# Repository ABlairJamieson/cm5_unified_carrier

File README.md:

# CM5 Unified Carrier

Carrier board for Radxa CM5 used in the Hyper-K camera system.

Features:
- 48V input
- PoE option
- USB3 camera interface
- Ethernet
- Uses drop in DC/DC modules for 48V->12V (ext power mode)
- Uses drop in DC/DC module for 12V->8V (IWCD camera)
- Uses drop in DC/DC module for 12V->5V (both cameras)

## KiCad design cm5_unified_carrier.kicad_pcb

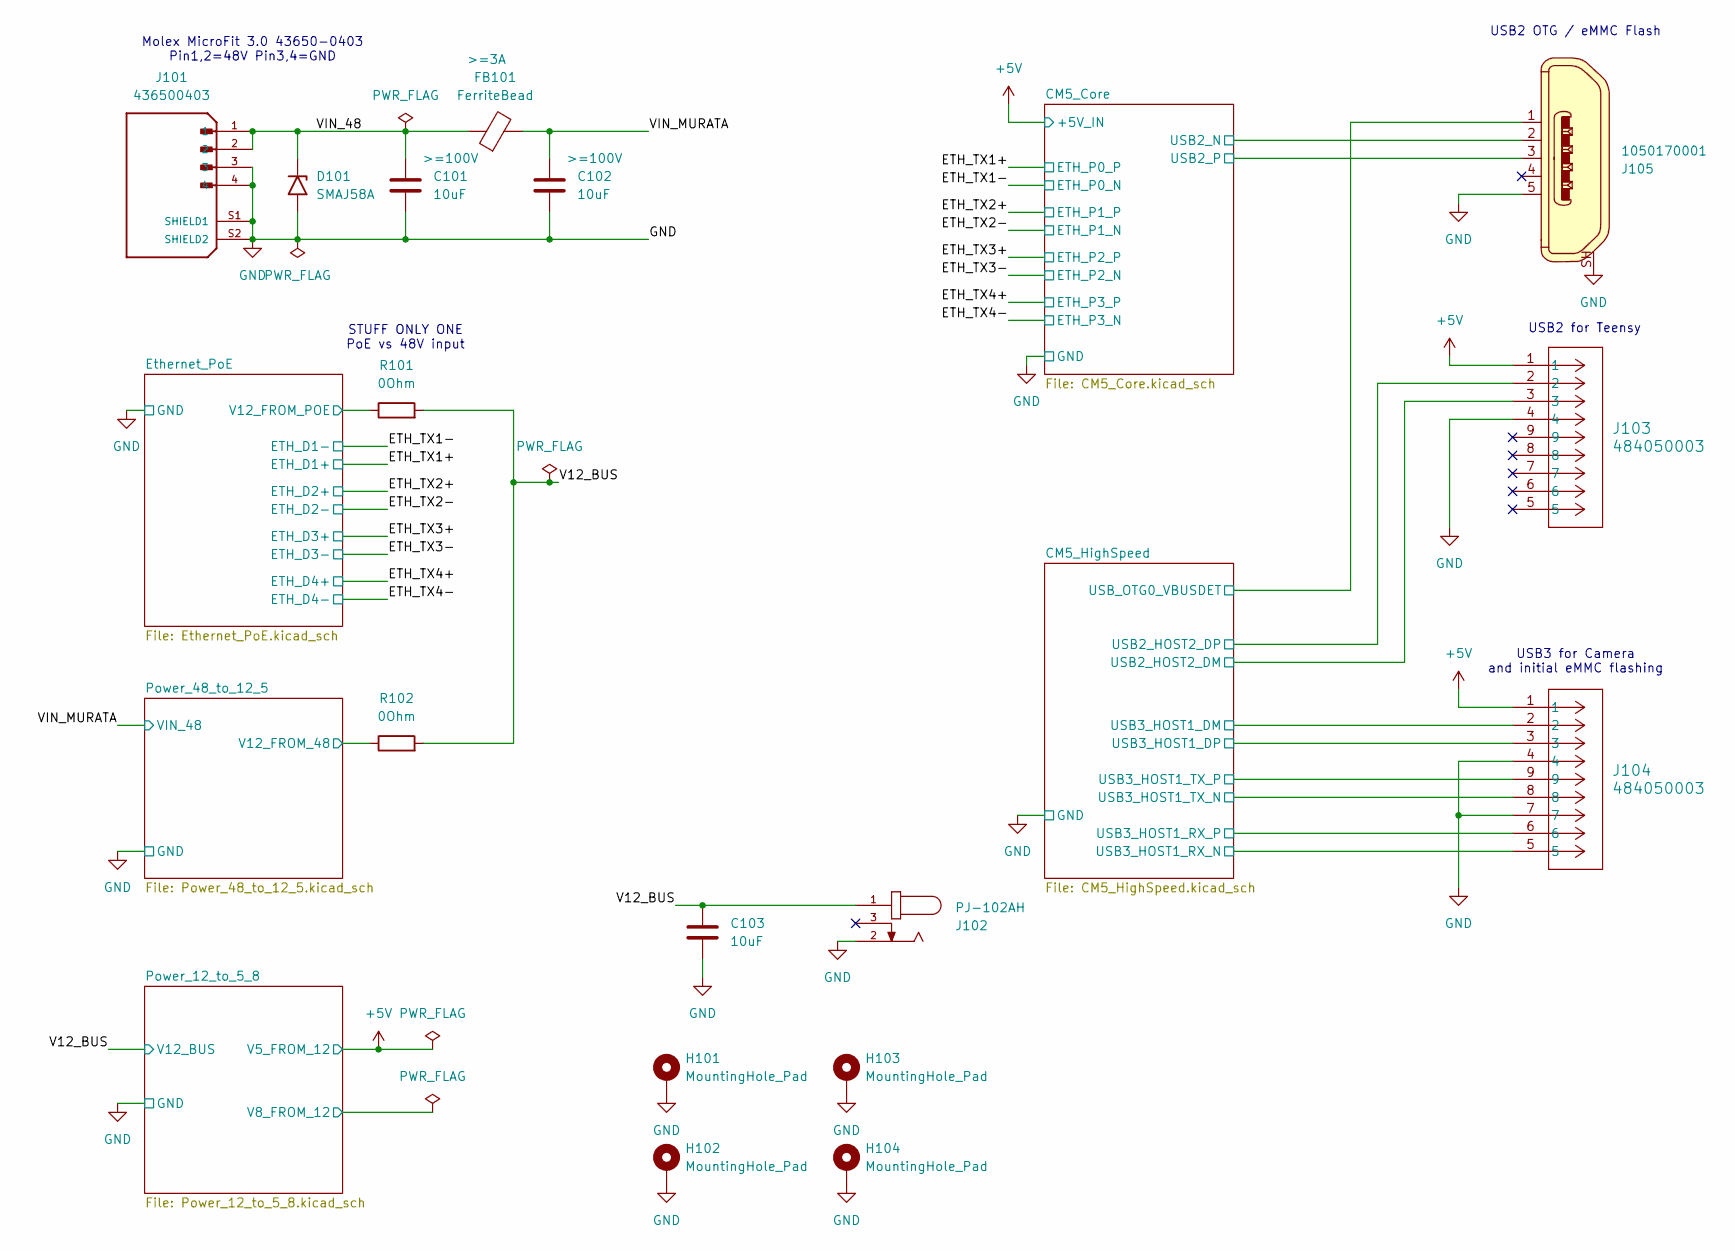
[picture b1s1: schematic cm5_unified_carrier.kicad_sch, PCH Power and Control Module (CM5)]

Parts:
C101, C102, C103: 10uF; C_1206_3216Metric_Pad1.33x1.80mm_HandSolder
D101: SMAJ58A; D_SMA
FB101: FerriteBead; FB_Wurth_WE-CBF-1206_W5.2
H101, H102, H103, H104: MountingHole_Pad; MountingHole_3.2mm_M3_DIN965_Pad
J101: 436500403; MOLEX_436500403; PARTREV F3
J102: PJ-102AH; CUI_PJ-102AH
J103, J104: 484050003; CONN_484050003_MOL
J105: 1050170001; USB_Micro_B_Female_1050170001; MPN 1050170001; Digi-Key_PN WM1399CT-ND
R101, R102: 0Ohm; R_1206_3216Metric_Pad1.30x1.75mm_HandSolder

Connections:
+5V: J103.1, J104.1; also elsewhere on the board
/CM5_Core/USB2_N: J105.2; also elsewhere on the board
/CM5_Core/USB2_P: J105.3; also elsewhere on the board
/CM5_HighSpeed/USB2_HOST2_DM: J103.3; also elsewhere on the board
/CM5_HighSpeed/USB2_HOST2_DP: J103.2; also elsewhere on the board
/CM5_HighSpeed/USB3_HOST1_DM: J104.2; also elsewhere on the board
/CM5_HighSpeed/USB3_HOST1_DP: J104.3; also elsewhere on the board
/CM5_HighSpeed/USB3_HOST1_SSRXN: J104.5; also elsewhere on the board
/CM5_HighSpeed/USB3_HOST1_SSRXP: J104.6; also elsewhere on the board
/CM5_HighSpeed/USB3_HOST1_SSTXN: J104.8; also elsewhere on the board
/CM5_HighSpeed/USB3_HOST1_SSTXP: J104.9; also elsewhere on the board
/CM5_HighSpeed/USB_OTG0_VBUSDET: J105.1; also elsewhere on the board
/Ethernet_PoE/V12_FROM_POE: R101.1; also elsewhere on the board
/Power_48_to_12_5/V12_FROM_48: R102.1; also elsewhere on the board
/V12_BUS: C103.1, J102.1, R101.2, R102.2; also elsewhere on the board
/VIN_48: C101.1, D101.1 (A1), FB101.1, J101.1, J101.2
/VIN_MURATA: C102.1, FB101.2; also elsewhere on the board
GND: C101.2, C102.2, C103.2, D101.2 (A2), H101.1, H102.1, H103.1, H104.1, J101.3, J101.4, J101.S1 (SHIELD1), J101.S2 (SHIELD2), J102.2, J103.4, J104.4, J104.7, J105.5, J105.SH; also elsewhere on the board

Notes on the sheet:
STUFF ONLY ONE PoE vs 48V input
USB2 for Teensy
USB2 OTG / eMMC Flash
USB3 for Camera and initial eMMC flashing
Molex MicroFit 3.0 43650-0403 Pin1,2=48V Pin3,4=GND

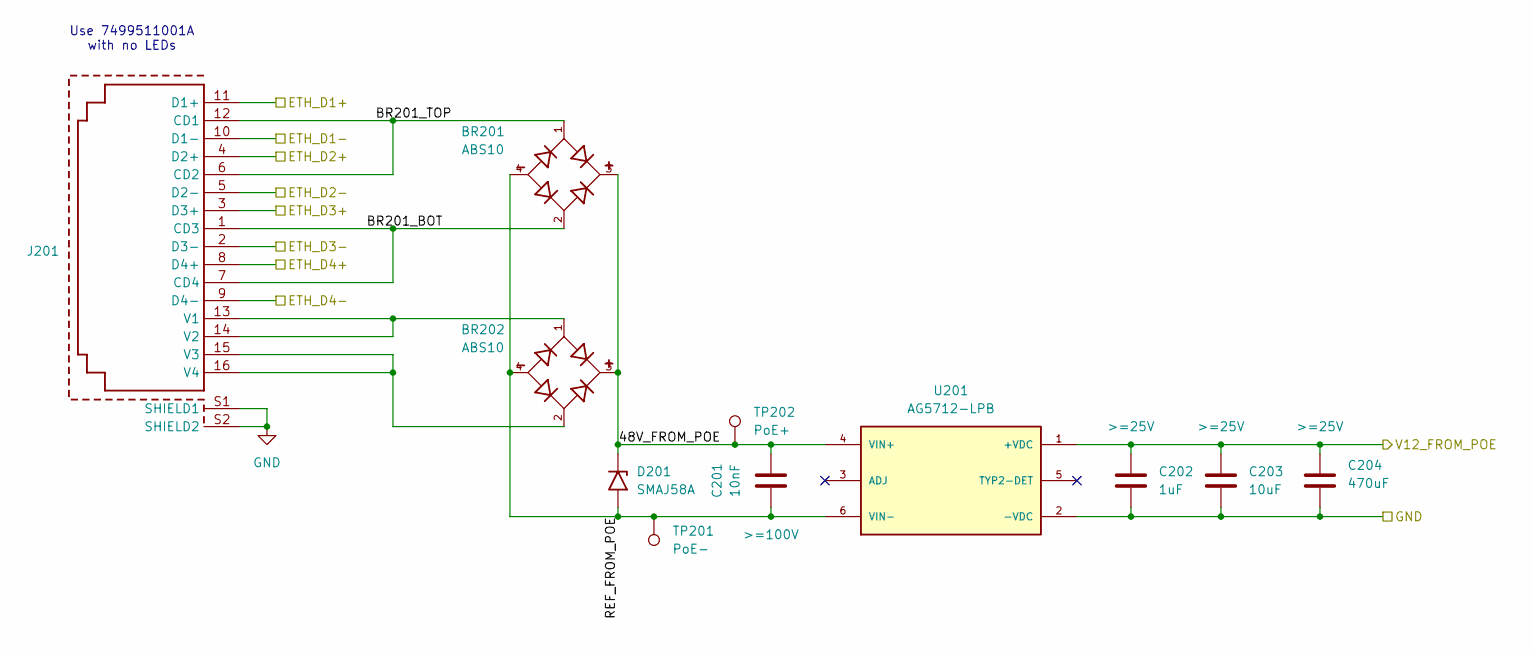
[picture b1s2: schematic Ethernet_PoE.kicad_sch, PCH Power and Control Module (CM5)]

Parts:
BR201, BR202: ABS10; SOT200P640X160-4N; PART_REV 4
C201: 10nF; C_1206_3216Metric_Pad1.33x1.80mm_HandSolder
C202: 1uF; C_0805_2012Metric_Pad1.18x1.45mm_HandSolder
C203: 10uF; C_1206_3216Metric_Pad1.33x1.80mm_HandSolder
C204: 470uF; CP_Elec_8x6.5
D201: SMAJ58A; D_SMA
J201: 7499511002A; T_Wurth_WE-RJ45LAN_7499511002A; Part Number 7499511002A
TP201: PoE-; TestPoint_Pad_D1.5mm
TP202: PoE+; TestPoint_Pad_D1.5mm
U201: AG5712-LPB; MODULE_AG5712-LPB; PARTREV V1.1

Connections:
/ETH_TX1+: J201.11 (D1+); also elsewhere on the board
/ETH_TX1-: J201.10 (D1-); also elsewhere on the board
/ETH_TX2+: J201.4 (D2+); also elsewhere on the board
/ETH_TX2-: J201.5 (D2-); also elsewhere on the board
/ETH_TX3+: J201.3 (D3+); also elsewhere on the board
/ETH_TX3-: J201.2 (D3-); also elsewhere on the board
/ETH_TX4+: J201.8 (D4+); also elsewhere on the board
/ETH_TX4-: J201.9 (D4-); also elsewhere on the board
/Ethernet_PoE/48V_FROM_POE: BR201.3, BR202.3, C201.2, D201.1 (A1), TP202.1, U201.4 (VIN+)
/Ethernet_PoE/BR201_BOT: BR201.2, J201.1 (CD3), J201.7 (CD4)
/Ethernet_PoE/BR201_TOP: BR201.1, J201.6 (CD2), J201.12 (CD1)
/Ethernet_PoE/REF_FROM_POE: BR201.4, BR202.4, C201.1, D201.2 (A2), TP201.1, U201.6 (VIN-)
/Ethernet_PoE/V12_FROM_POE: C202.1, C203.1, C204.1, U201.1 (+VDC); also elsewhere on the board
GND: C202.2, C203.2, C204.2, J201.S1 (SHIELD1), J201.S2 (SHIELD2), U201.2 (-VDC); also elsewhere on the board
unnamed: BR202.1, J201.13 (V1), J201.14 (V2)
unnamed: BR202.2, J201.15 (V3), J201.16 (V4)

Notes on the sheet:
Use 7499511001A with no LEDs

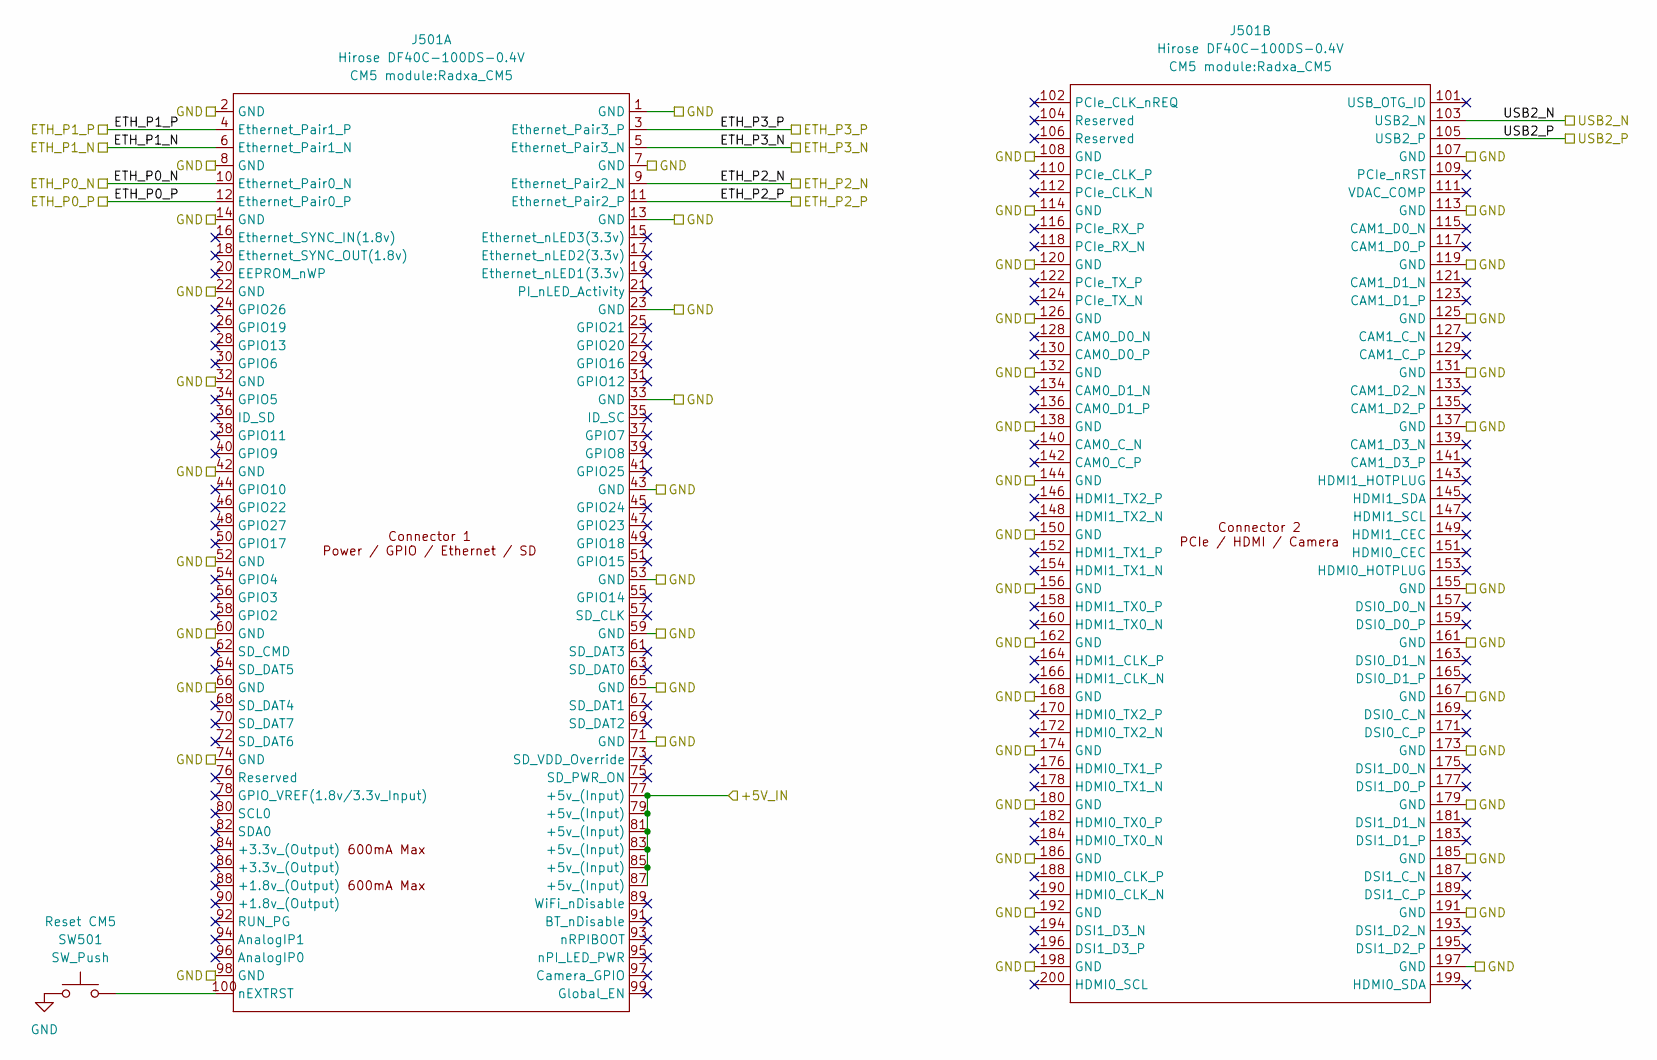
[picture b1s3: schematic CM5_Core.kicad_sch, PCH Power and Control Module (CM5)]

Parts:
J501: Hirose DF40C-100DS-0.4V; Radxa_CM5
SW501: SW_Push; SW_SPST_EVQP7A

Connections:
+5V: J501.77 (+5v_(Input)), J501.79 (+5v_(Input)), J501.81 (+5v_(Input)), J501.83 (+5v_(Input)), J501.85 (+5v_(Input)), J501.87 (+5v_(Input)); also elsewhere on the board
/CM5_Core/USB2_N: J501.103 (USB2_N); also elsewhere on the board
/CM5_Core/USB2_P: J501.105 (USB2_P); also elsewhere on the board
/ETH_TX1+: J501.12 (Ethernet_Pair0_P); also elsewhere on the board
/ETH_TX1-: J501.10 (Ethernet_Pair0_N); also elsewhere on the board
/ETH_TX2+: J501.4 (Ethernet_Pair1_P); also elsewhere on the board
/ETH_TX2-: J501.6 (Ethernet_Pair1_N); also elsewhere on the board
/ETH_TX3+: J501.11 (Ethernet_Pair2_P); also elsewhere on the board
/ETH_TX3-: J501.9 (Ethernet_Pair2_N); also elsewhere on the board
/ETH_TX4+: J501.3 (Ethernet_Pair3_P); also elsewhere on the board
/ETH_TX4-: J501.5 (Ethernet_Pair3_N); also elsewhere on the board
GND: J501.1 (GND), J501.2 (GND), J501.7 (GND), J501.8 (GND), J501.13 (GND), J501.14 (GND), J501.22 (GND), J501.23 (GND), J501.32 (GND), J501.33 (GND), J501.42 (GND), J501.43 (GND), J501.52 (GND), J501.53 (GND), J501.59 (GND), J501.60 (GND), J501.65 (GND), J501.66 (GND), J501.71 (GND), J501.74 (GND), J501.98 (GND), J501.107 (GND), J501.108 (GND), J501.113 (GND), J501.114 (GND), J501.119 (GND), J501.120 (GND), J501.125 (GND), J501.126 (GND), J501.131 (GND), J501.132 (GND), J501.137 (GND), J501.138 (GND), J501.144 (GND), J501.150 (GND), J501.155 (GND), J501.156 (GND), J501.161 (GND), J501.162 (GND), J501.167 (GND), J501.168 (GND), J501.173 (GND), J501.174 (GND), J501.179 (GND), J501.180 (GND), J501.185 (GND), J501.186 (GND), J501.191 (GND), J501.192 (GND), J501.197 (GND), J501.198 (GND), SW501.1; also elsewhere on the board
unnamed: J501.100 (nEXTRST), SW501.2

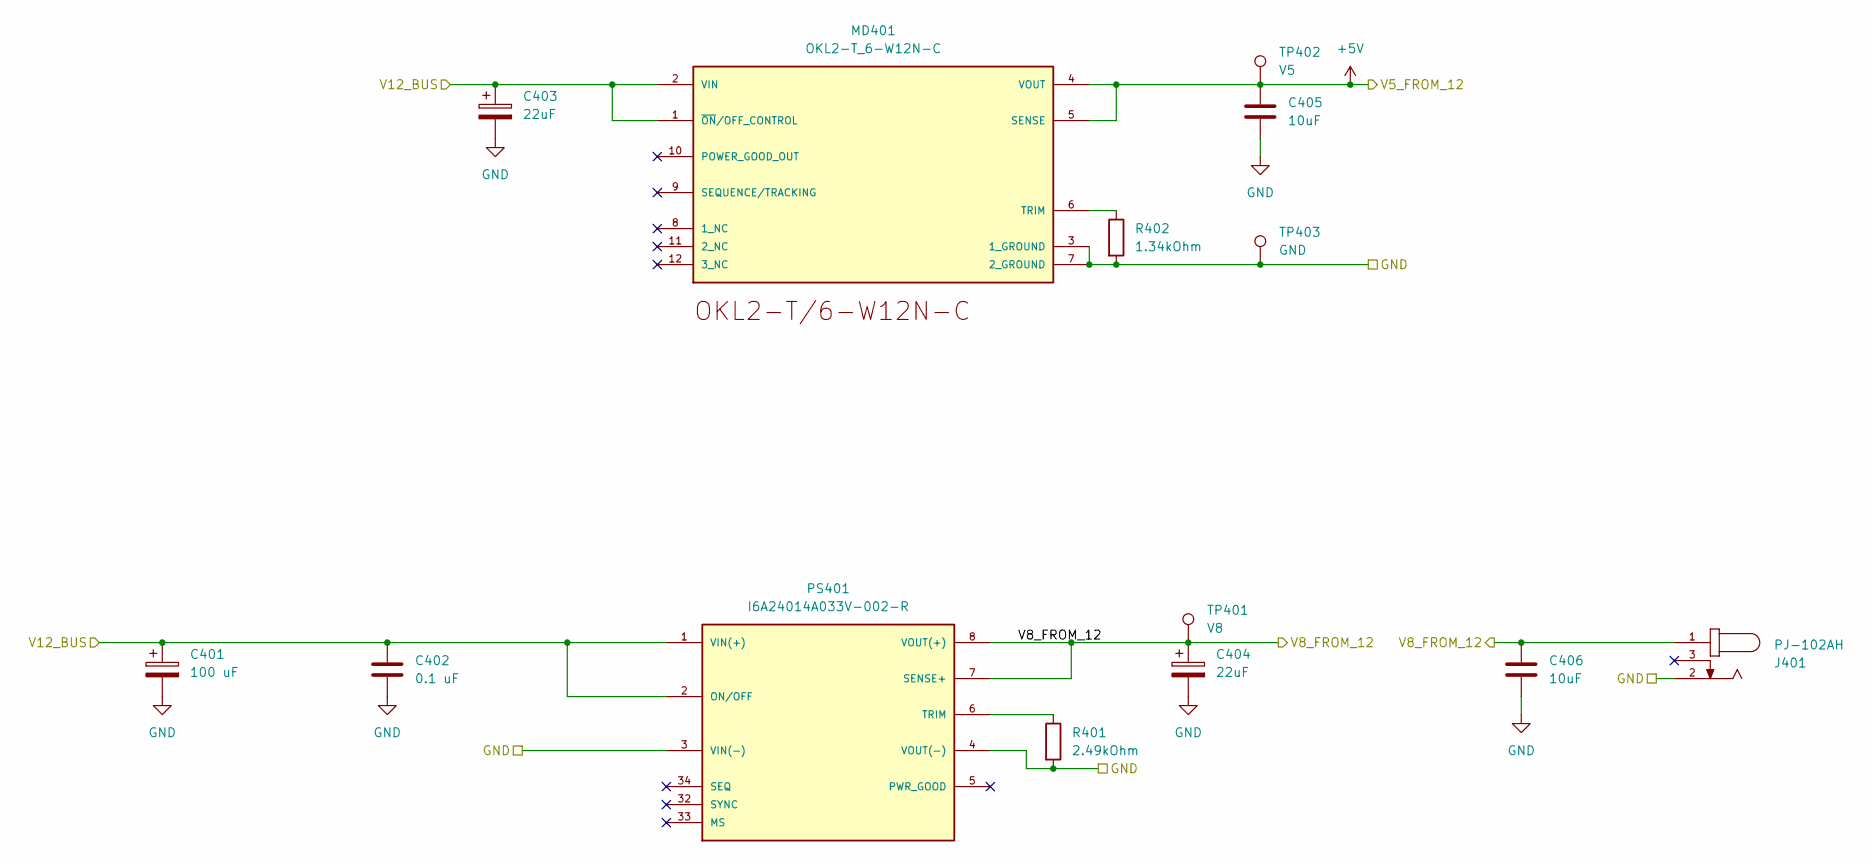
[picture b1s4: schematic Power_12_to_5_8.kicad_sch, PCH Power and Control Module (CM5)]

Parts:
C401: 100 uF; CP_Elec_6.3x5.8
C402: 0.1 uF; C_0805_2012Metric_Pad1.18x1.45mm_HandSolder
C403, C404: 22uF; C_1206_3216Metric_Pad1.33x1.80mm_HandSolder
C405, C406: 10uF; C_1206_3216Metric_Pad1.33x1.80mm_HandSolder
J401: PJ-102AH; CUI_PJ-102AH
MD401: OKL2-T_6-W12N-C; MURATA_OKL2-T-6-W12N-C_0; MOUSER_PART_NUMBER 580-OKL2-T/6-W12N-C; MOUSER_DESCRIPTION Non-Isolated DC/DC Converters 12Vin .59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
PS401: I6A24014A033V-002-R; CONV_I6A24014A033V-002-R; PARTREV A2; DigiKey_Part_Number 285-2857-ND
R401: 2.49kOhm; R_0805_2012Metric_Pad1.20x1.40mm_HandSolder
R402: 1.34kOhm; R_0805_2012Metric_Pad1.20x1.40mm_HandSolder
TP401: V8; TestPoint_Pad_D1.5mm
TP402: V5; TestPoint_Pad_D1.5mm
TP403: GND; TestPoint_Pad_D1.5mm

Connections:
+5V: C405.1, MD401.4 (VOUT), MD401.5 (SENSE), TP402.1; also elsewhere on the board
/Power_12_to_5_8/V8_FROM_12: C404.1, C406.1, J401.1, PS401.7 (SENSE+), PS401.8 (VOUT(+)), TP401.1
/V12_BUS: C401.1, C402.1, C403.1, MD401.1 (~ON/OFF_CONTROL), MD401.2 (VIN), PS401.1 (VIN(+)), PS401.2 (ON/OFF); also elsewhere on the board
GND: C401.2, C402.2, C403.2, C404.2, C405.2, C406.2, J401.2, MD401.3 (1_GROUND), MD401.7 (2_GROUND), PS401.3 (VIN(-)), PS401.4 (VOUT(-)), R401.2, R402.2, TP403.1; also elsewhere on the board
unnamed: MD401.6 (TRIM), R402.1
unnamed: PS401.6 (TRIM), R401.1

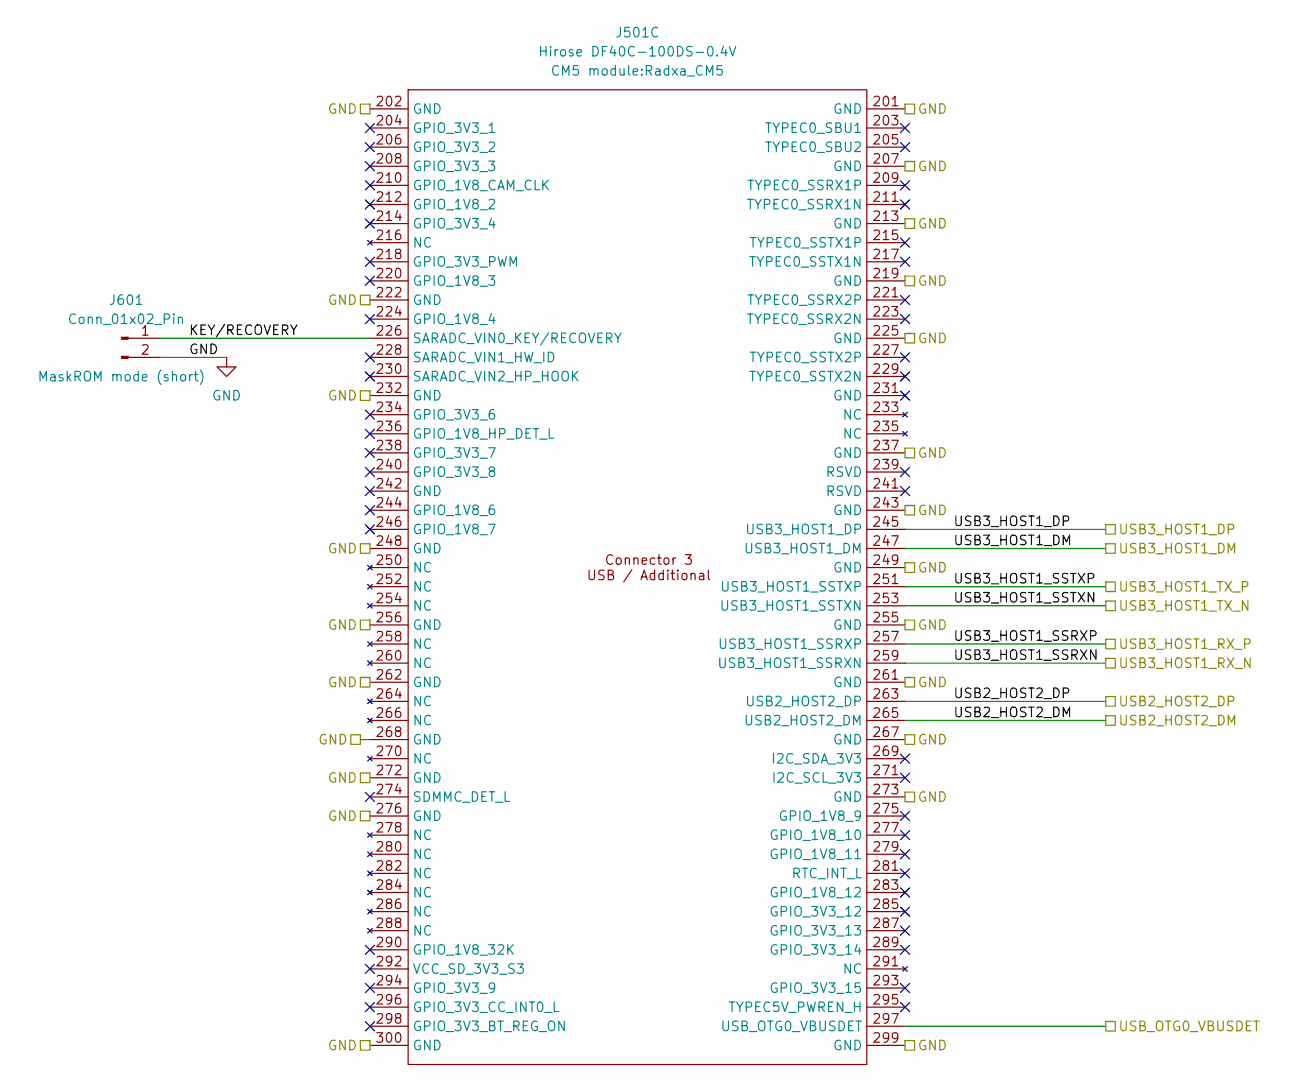
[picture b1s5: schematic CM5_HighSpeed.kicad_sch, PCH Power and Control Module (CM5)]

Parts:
J501: Hirose DF40C-100DS-0.4V; Radxa_CM5
J601: Conn_01x02_Pin; PinHeader_1x02_P2.54mm_Vertical

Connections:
/CM5_HighSpeed/KEY/RECOVERY: J501.226 (SARADC_VIN0_KEY/RECOVERY), J601.1
/CM5_HighSpeed/USB2_HOST2_DM: J501.265 (USB2_HOST2_DM); also elsewhere on the board
/CM5_HighSpeed/USB2_HOST2_DP: J501.263 (USB2_HOST2_DP); also elsewhere on the board
/CM5_HighSpeed/USB3_HOST1_DM: J501.247 (USB3_HOST1_DM); also elsewhere on the board
/CM5_HighSpeed/USB3_HOST1_DP: J501.245 (USB3_HOST1_DP); also elsewhere on the board
/CM5_HighSpeed/USB3_HOST1_SSRXN: J501.259 (USB3_HOST1_SSRXN); also elsewhere on the board
/CM5_HighSpeed/USB3_HOST1_SSRXP: J501.257 (USB3_HOST1_SSRXP); also elsewhere on the board
/CM5_HighSpeed/USB3_HOST1_SSTXN: J501.253 (USB3_HOST1_SSTXN); also elsewhere on the board
/CM5_HighSpeed/USB3_HOST1_SSTXP: J501.251 (USB3_HOST1_SSTXP); also elsewhere on the board
/CM5_HighSpeed/USB_OTG0_VBUSDET: J501.297 (USB_OTG0_VBUSDET); also elsewhere on the board
GND: J501.201 (GND), J501.202 (GND), J501.207 (GND), J501.213 (GND), J501.219 (GND), J501.222 (GND), J501.225 (GND), J501.232 (GND), J501.237 (GND), J501.243 (GND), J501.248 (GND), J501.249 (GND), J501.255 (GND), J501.256 (GND), J501.261 (GND), J501.262 (GND), J501.267 (GND), J501.268 (GND), J501.272 (GND), J501.273 (GND), J501.276 (GND), J501.299 (GND), J501.300 (GND), J601.2; also elsewhere on the board

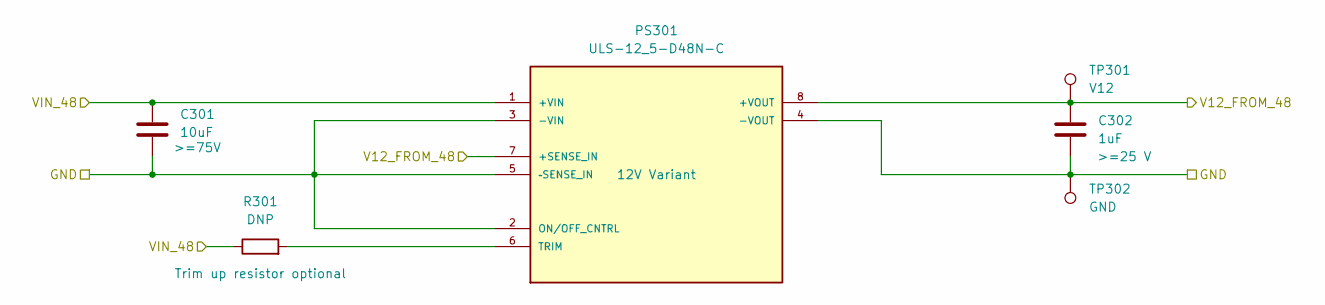
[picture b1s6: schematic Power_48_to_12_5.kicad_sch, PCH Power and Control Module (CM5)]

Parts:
C301: 10uF; CP_Elec_6.3x5.4
C302: 1uF; C_0805_2012Metric_Pad1.18x1.45mm_HandSolder
PS301: ULS-12_5-D48N-C; CONV_ULS-12_5-D48N-C
R301: DNP; R_0805_2012Metric_Pad1.20x1.40mm_HandSolder
TP301: V12; TestPoint_Pad_D1.5mm
TP302: GND; TestPoint_Pad_D1.5mm

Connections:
/Power_48_to_12_5/V12_FROM_48: C302.1, PS301.7 (+SENSE_IN), PS301.8 (+VOUT), TP301.1; also elsewhere on the board
/VIN_MURATA: C301.1, PS301.1 (+VIN), R301.1; also elsewhere on the board
GND: C301.2, C302.2, PS301.2 (ON/OFF_CNTRL), PS301.3 (-VIN), PS301.4 (-VOUT), PS301.5 (–SENSE_IN), TP302.1; also elsewhere on the board
unnamed: PS301.6 (TRIM), R301.2

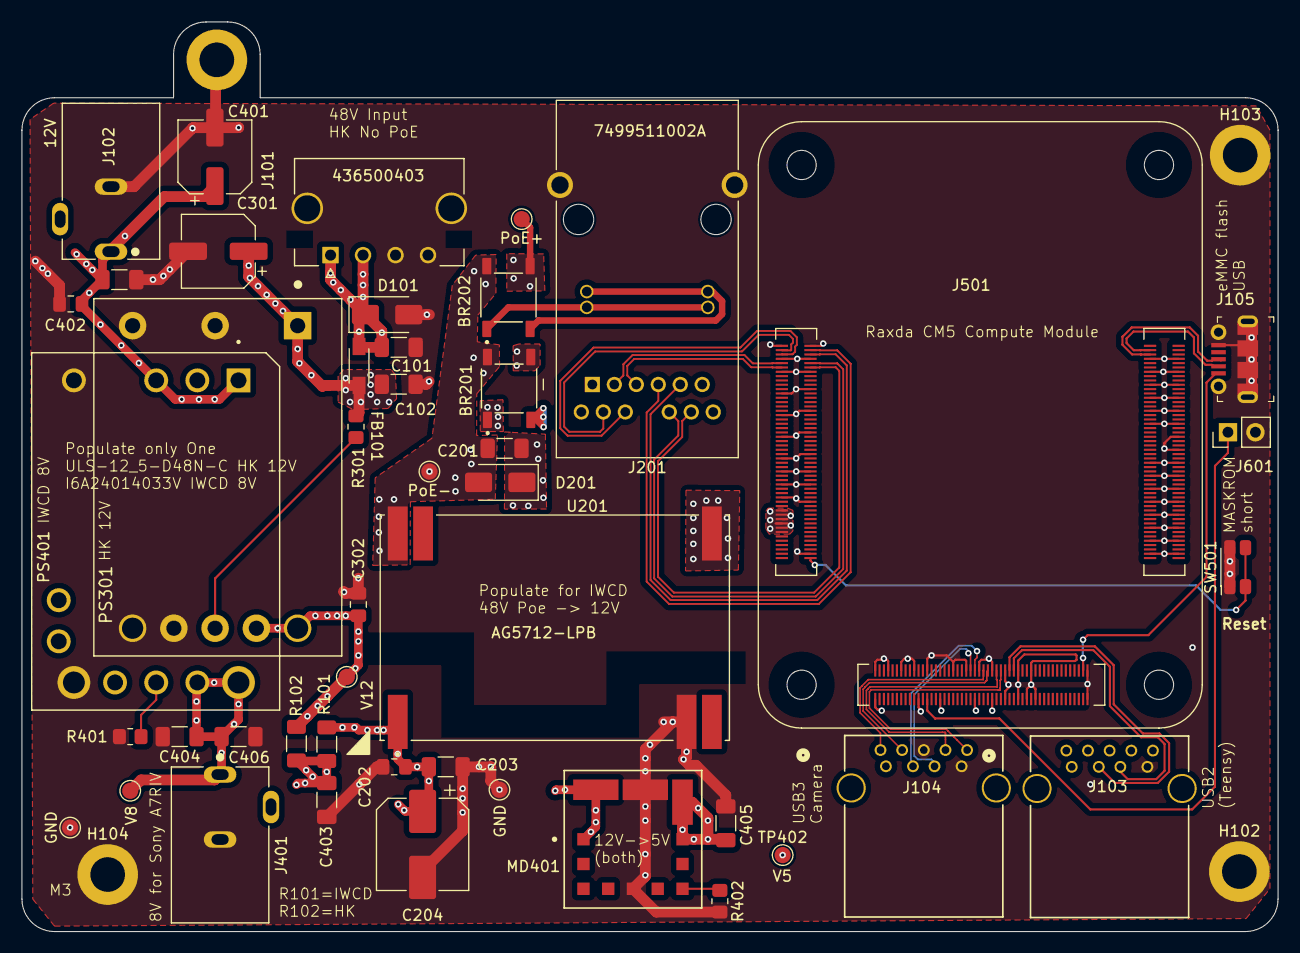
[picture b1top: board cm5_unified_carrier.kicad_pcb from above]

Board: 4 copper layers, 116.0 x 84.0 mm, 50 parts (0 on the bottom side), 38 nets.

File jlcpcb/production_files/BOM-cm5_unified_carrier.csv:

Comment,Designator,Footprint,LCSC,Quantity
0Ohm,"R101,R102",R_1206_3216Metric_Pad1.30x1.75mm_HandSolder,C17888,2
10uF,"C101,C102,C103,C406",C_1206_3216Metric_Pad1.33x1.80mm_HandSolder,C89632,4
1uF,C302,C_0805_2012Metric_Pad1.18x1.45mm_HandSolder,C28323,1
22uF,C404,C_1206_3216Metric_Pad1.33x1.80mm_HandSolder,C12891,1
484050003,J103,CONN_484050003_MOL,C6058327,1
SMAJ58A,"D101,D201",D_SMA,C151246,2
PJ-102AH,J102,CUI_PJ-102AH,,1
7499511002A,J201,T_Wurth_WE-RJ45LAN_7499511002A,,1
436500403,J101,MOLEX_436500403,,1
AG5712-LPB,U201,MODULE_AG5712-LPB,,1
GND,TP403,TestPoint_Pad_D1.5mm,,1
V8,TP401,TestPoint_Pad_D1.5mm,,1
GND,TP302,TestPoint_Pad_D1.5mm,,1
V12,TP301,TestPoint_Pad_D1.5mm,,1
1.34kOhm,R402,R_0805_2012Metric_Pad1.20x1.40mm_HandSolder,,1
2.49kOhm,R401,R_0805_2012Metric_Pad1.20x1.40mm_HandSolder,,1
DNP,R301,R_0805_2012Metric_Pad1.20x1.40mm_HandSolder,,1
I6A24014A033V-002-R,PS401,CONV_I6A24014A033V-002-R,,1
ULS-12_5-D48N-C,PS301,CONV_ULS-12_5-D48N-C,,1
OKL2-T_6-W12N-C,MD401,MURATA_OKL2-T-6-W12N-C_0,,1
PJ-102AH,J401,CUI_PJ-102AH,,1
FerriteBead,FB101,FB_Wurth_WE-CBF-1206_W5.2,,1
10uF,C405,C_1206_3216Metric_Pad1.33x1.80mm_HandSolder,,1
22uF,C403,C_1206_3216Metric_Pad1.33x1.80mm_HandSolder,,1
0.1 uF,C402,C_0805_2012Metric_Pad1.18x1.45mm_HandSolder,,1
100 uF,C401,CP_Elec_6.3x5.8,,1
10uF,C301,CP_Elec_6.3x5.4,,1
470uF,C204,CP_Elec_8x6.5,,1
10uF,C203,C_1206_3216Metric_Pad1.33x1.80mm_HandSolder,,1
1uF,C202,C_0805_2012Metric_Pad1.18x1.45mm_HandSolder,,1
10nF,C201,C_1206_3216Metric_Pad1.33x1.80mm_HandSolder,,1
Hirose DF40C-100DS-0.4V,J501,Radxa_CM5,,1
484050003,J104,CONN_484050003_MOL,,1
1050170001,J105,USB_Micro_B_Female_1050170001,,1
Conn_01x02_Pin,J601,PinHeader_1x02_P2.54mm_Vertical,,1
SW_Push,SW501,SW_SPST_EVQP7A,,1
V5,TP402,TestPoint_Pad_D1.5mm,,1
PoE+,TP202,TestPoint_Pad_D1.5mm,,1
PoE-,TP201,TestPoint_Pad_D1.5mm,,1
ABS10,BR201,SOT200P640X160-4N,,1
ABS10,BR202,SOT200P640X160-4N,,1

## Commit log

2026-03-09 Initial commit: CM5 carrier for camera control
2026-03-09 Add a short readme
2026-03-09 Add image to README for visual reference
2026-03-09 Added another barrel jack for 12V output for ASI camera
2026-03-09 Replace image source in README.md
    Updated image in README with a new source.
2026-03-09 Add new image to README.md
2026-03-09 Added USB connector for flashing eMMC and related switches
2026-03-10 Reduced board size by allowing overlap of power modules where only one needs to be populated
2026-03-10 Add image to README for enhanced documentation
    Added an image to the README for better visualization.
2026-03-10 minor cleanup
2026-03-10 a few more minor updates
2026-03-10 Add image to README for enhanced documentation
    Added a new image to the README for better visualization.
2026-04-09 Update to fix power connection mistakes in both IWCD and HK configurations. For IWCD added bridge rectifier diodes needed for PoE, for HK updated to look at correct ref voltage for the 12V generation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
